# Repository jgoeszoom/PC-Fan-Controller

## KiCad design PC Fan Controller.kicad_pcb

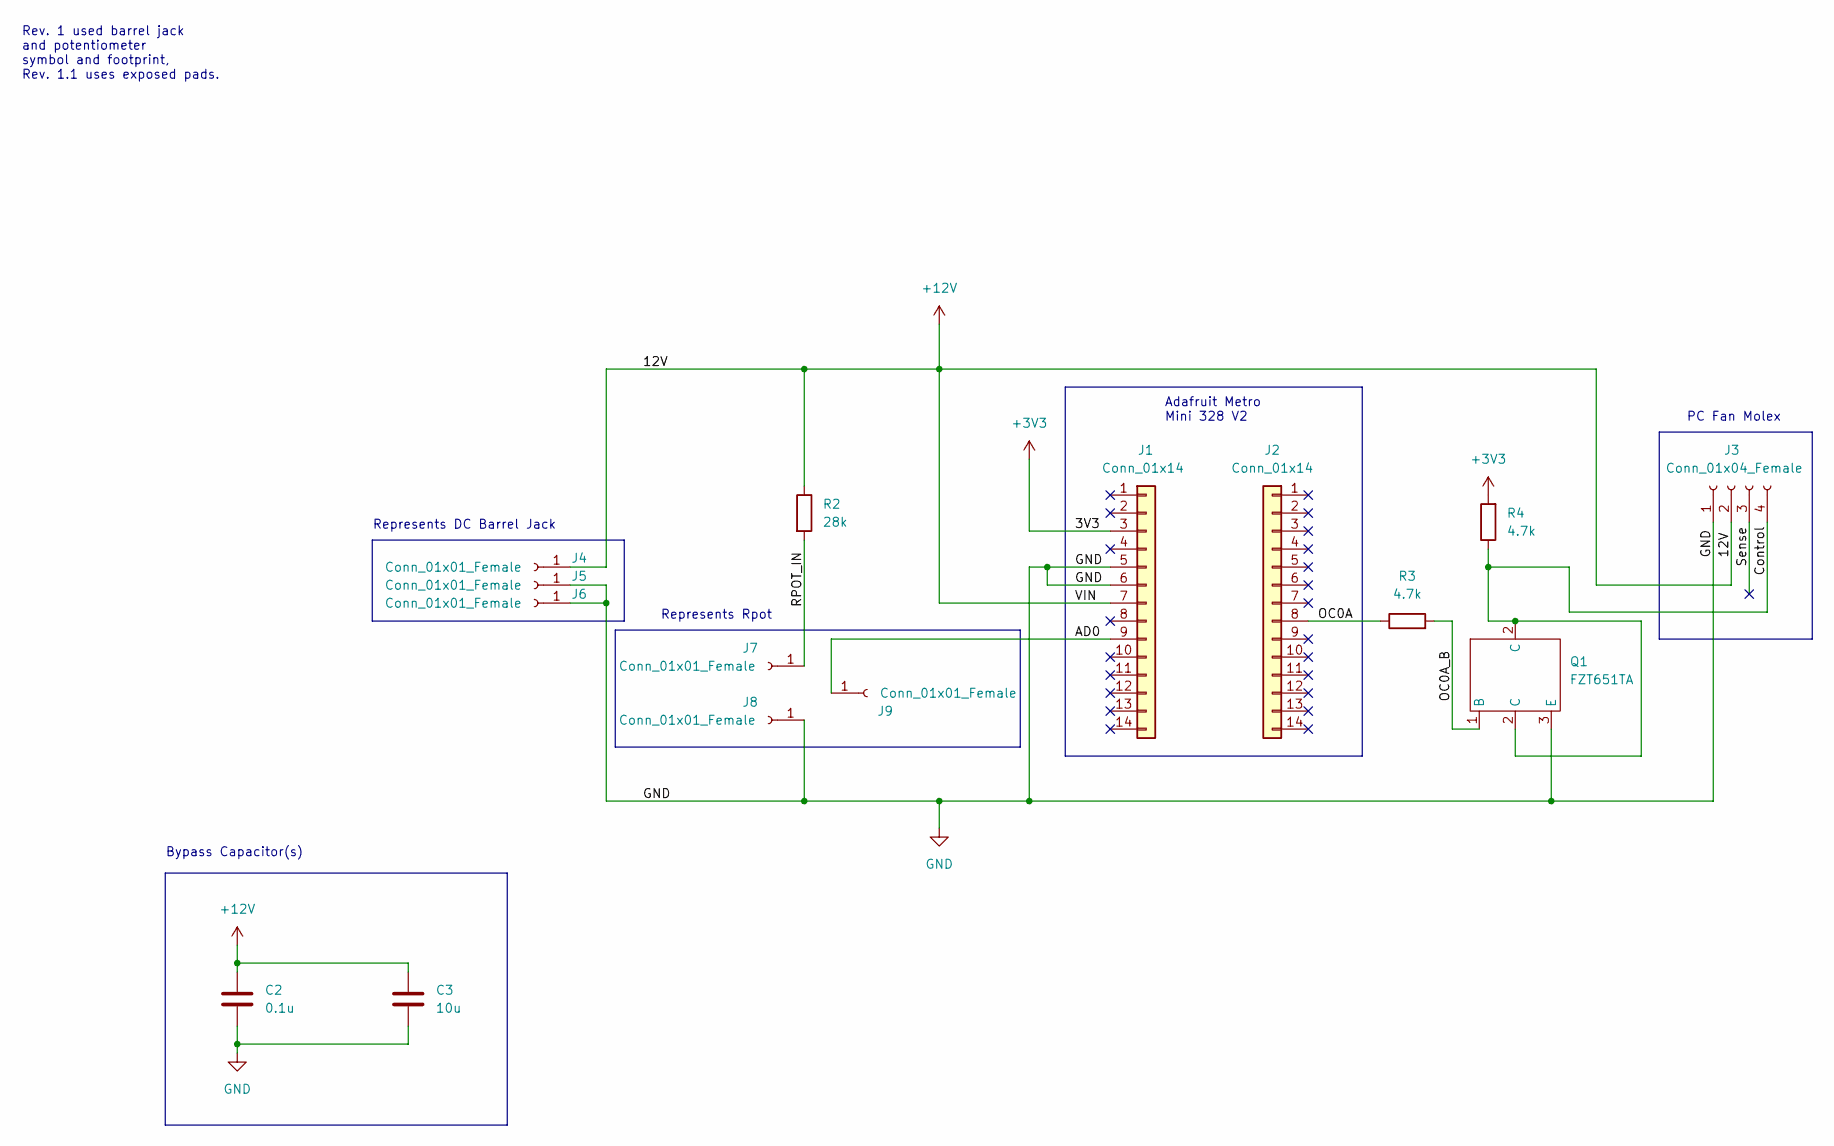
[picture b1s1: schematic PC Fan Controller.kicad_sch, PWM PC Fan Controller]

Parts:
C2: 0.1u; C_Disc_D5.0mm_W2.5mm_P5.00mm
C3: 10u; C_Disc_D5.0mm_W2.5mm_P5.00mm
J1, J2: Conn_01x14; PinSocket_1x14_P2.54mm_Vertical
J3: Conn_01x04_Female; Molex_KK-254_AE-6410-04A_1x04_P2.54mm_Vertical
J4, J5, J6: Conn_01x01_Female; TestPoint_Pad_4.0x4.0mm
J7, J8, J9: Conn_01x01_Female; TestPoint_Pad_3.0x3.0mm
Q1: FZT651TA; SOT-223-3_TabPin2
R2: 28k; R_Axial_DIN0207_L6.3mm_D2.5mm_P10.16mm_Horizontal
R3, R4: 4.7k; R_Axial_DIN0207_L6.3mm_D2.5mm_P10.16mm_Horizontal

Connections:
+3V3: J1.3, R4.2
+12V: C2.1, C3.1, J1.7, J3.2, J4.1, R2.1
/AD0: J1.9, J9.1
/Control: J3.4, Q1.2 (C), R4.1
/OC0A: J2.8, R3.1
/OC0A_B: Q1.1 (B), R3.2
/RPOT_IN: J7.1, R2.2
/Sense: J3.3
GND: C2.2, C3.2, J1.5, J1.6, J3.1, J5.1, J6.1, J8.1, Q1.3 (E)

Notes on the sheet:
Bypass Capacitor(s)
PC Fan Molex
Represents DC Barrel Jack
Rev. 1 used barrel jack and potentiometer symbol and footprint, Rev. 1.1 uses exposed pads.
Represents Rpot
Adafruit Metro Mini 328 V2

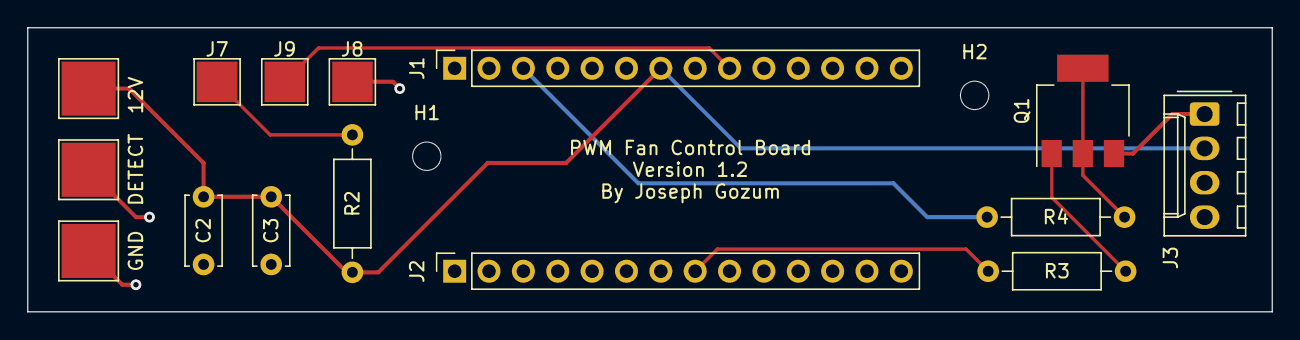
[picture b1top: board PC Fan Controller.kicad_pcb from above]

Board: 2 copper layers, 92.0 x 21.0 mm, 17 parts (0 on the bottom side), 8 nets.

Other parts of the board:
H1, H2: MountingHole_2.1mm

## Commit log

2022-10-16 Updated .gitnore
2022-10-16 Added folders for the PDFs of the board and schematic
